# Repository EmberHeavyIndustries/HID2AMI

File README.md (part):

## ** Preassembled units **: If you are interested in ready-to-go pre-assembled units, a small number of them is available from time to time, assembled by various users/hobbyists. You can look for one on Amibay's thread [link] and check if there is any available on sale (https://www.amibay.com/threads/new-hid2ami-v3-1-0-mousewheel-support-personality-switch-hid-mouse-and-gamepad-to-amiga-adaptor.2451017/) 

||||
| ------------------------------ | ---------------------------------------------- | --------------------------- |

**HID2AMI** is an **HID mouse to quadrature waveform converter** and **HID Gamepad adapter** for the Amiga (and C64, Atari 7600, AtariST also..) series of boards; it allows ANY modern HID mouse (not limited to PS/2-USB) and almost ANY (*) modern digital/analog Gamepad to be connected and enjoyed with our Amiga computers.

(*) At the moment it has been tested against dozens of different gamepads,  but working for each and every existing Gamepad cannot be guaranteed; nevertheless, if you find a Pad which does not work with HID2AMI, you are encouraged to contact the author and supply him its "HID Report Descriptor" to be investigated.

[HOW TO SUBMIT AN HID DUMP ](https://github.com/EmberHeavyIndustries/HID2AMI/blob/master/Docs/hid.dump.howto.md)

## **ENABLING MOUSEWHEEL SUPPORT**

In order the mousewheel events to be recognized from Amiga side, a proper driver has to be installed on Amiga.

The driver is freely available, and can be downloaded from the FIRMWARE folder on this github

## **REV 3.1 board** 

HID2AMI Rev. 3.1 board (released in February 2025) upgrades previous versions by compacting the size and layout to the tiniest possible, plus adding the capability to switch firmware functions on the fly.

Rev. 3.1.0 comes with the new fromware v4.0.0 which adds the capability to switch among AMIGA - ATARI_ST - C64 behavior, with peculiar features for each.
All V4.x series firmwares will be backward compatible with V2 and V1 boards

|      Personality      |         SW1 | SW2  | SW3          |           Notes                                    | 
| --------------------- |      :---:  | :---:| :---:        |        ---                                         |  
| Amiga                 |         OFF |  OFF |   X          | Default Classic HID2AMI                            | 
| Atari ST              |         ON  |  OFF |   X          | ST Mouse and Joystick/Joypad                       |
| C64                   |         OFF |  ON  |   X          | C64 Joystick/Joypad with 2nd button                |
| CONTROLLER PRIORITY   |          X  |   X  |   OFF/ON     | J->M->K / K->J->M 	                             |

## **Lemaru's shell case (Rev 3.x boards only)** 

Thanks to the talented friend Lemaru, an awesome cover is available for everyone.

You are free to download the stl/step files linked below, and print your own copy of this awesome accessory !

[ShellBox30 Top](https://github.com/EmberHeavyIndustries/HID2AMI/blob/master/Docs/HID2AmiV3_Base.stl)

[Shellbox30 Bottom](https://github.com/EmberHeavyIndustries/HID2AMI/blob/master/Docs/HID2AmiV3_Lid.stl)

## **REV 2.0 board** 

HID2AMI Rev. 2.0 board (released in Autumn 2022) upgrades previous versions by adding capability of supporting Mousewheel and CD32 protocols, in a smaller compact shape.

Current firmware v3.0.0 act in the very same way of v1.x.x, with Mousewheel support (CD32 support  will be added in future releases)

!
!
!

(Transparent shellcase images courtesy by IAmAddict)

## **NEW v3.0.0 FIRMWARE WITH MOUSEWHEEL SUPPORT** 

Starting from v3.0.0 firmware, support for mousewheel to ANY adapter hw revision (v1.0, v1.1, V2.0) has been added.

The firmware can be directly flashed on all revisions, and enables native Mousewheel support in v2.0.

In order to enable Mousewheel support on v1.x revisions, a couple of little hacks must be performed on the boards.
The hacks to be performed are: 
- short two adiacent pins of the STM32 microprocessr, by mean of a tiny drop of solder alloy (see pic)
- remove Q2 mosfet and shorten two of the pads (see pic)

After the mod, mousewheel works in v1.x all the same way it works in v2.0.
Though the mod is quite trivial, it need a minimal soldering experience.
I cannot be held responsible if anybody damages his board(s) while not properly performing the mod.

In order the mousewheel events to be recognized from Amiga side, a proper driver has to be installed on Amiga.

The driver is freely available, and can be downloaded from the FIRMWARE folder on this github

## **REV 1.1 board** 

## **Ember Heavy Industries's official Open source shell case (Rev 2.x boards only)** 

You are free to download the stl/step files linked below, and print your own copy of this beautiful shell cover !

(Sample 3D print by Solaris104)

(Sample 3D print by IAmAddicted)

[ShellBox Top](https://github.com/EmberHeavyIndustries/HID2AMI/blob/master/Docs/HID2AMI_ShellUpper.stl)

[Shellbox Bottom](https://github.com/EmberHeavyIndustries/HID2AMI/blob/master/Docs/HID2AMI_ShellLower.stl)

## **CERV's free shell case (Rev 2.x boards only)** 

User Cerv kindly designed and shared his alternative box design !

[ShellBox Cover](https://github.com/EmberHeavyIndustries/HID2AMI/blob/master/Docs/HID2AMI_CERV_cover.stl)

[Shellbox Case](https://github.com/EmberHeavyIndustries/HID2AMI/blob/master/Docs/HID2AMI_CERV_box.stl)

## **Ember Heavy Industries's official Open source shell case (Rev 1.1 boards only)** 

#### Based upon Lemaru's shell, with some enhancements and eye-catching HID2AMI logo carved on top  !

You are free to download the stl/step files linked below, and print your own copy of this beautiful shell cover !

[ShellBox Top](https://github.com/EmberHeavyIndustries/HID2AMI/blob/master/Docs/88.EmberHID2AMI.UpperShell_1.stl)

[Shellbox Bottom](https://github.com/EmberHeavyIndustries/HID2AMI/blob/master/Docs/88.EmberHID2AMI.LowerShell_1.stl)

## **GothDevil's Open source shell case (Rev 1.1 boards only)** 

#### Thanks to the talented and friendly user **GothDevil** for creating and sharing her precious work  !

You are free to download the stl/step files linked below, and print your own copy of this beautiful shell cover !

[ShellBox Top](https://github.com/EmberHeavyIndustries/HID2AMI/blob/master/Docs/top_cover_final.stl)

[Shellbox Bottom](https://github.com/EmberHeavyIndustries/HID2AMI/blob/master/Docs/bottom_cover_final.stl)

#### GothDevil kindly allows free and open distribution of this excellent work; nevertheless I (EmberHeavyIndustries) would consider it fair if anyone who enjoys her effort would give her a little donation (say: 1 EUR) to thank her for sharing.
Please send donations to GothDevil's paypal account here:

| ||Thank you GothDevil !|
| ------------------------------ | ---------------------------------------------- | --------------------------- |

## **Lemaru's Open source shell case (Rev 1.1 boards only)** 

#### Thanks to the talented and friendly user **Lemaru** for creating and sharing his precious work  !
!

You are free to download the stl/step files linked below, and print your own copy of this beautiful shell cover !

[ShellBox Top](https://github.com/EmberHeavyIndustries/HID2AMI/blob/master/Docs/HID2AMI_Top.stl)

[Shellbox Bottom](https://github.com/EmberHeavyIndustries/HID2AMI/blob/master/Docs/HID2AMI_Bottom.stl)

## **HOW DOES IT WORK** (in brief):

HID2AMI recognizes and manages any HID device connected to its USB interface; if the device is recognized as an HID mouse, then HID2AMI starts capturing live movements and button pressings of the peripheral, then converting both of them into proper quadrature waveforms (and Amiga mouse button pressings) which can be properly understood by the Amiga itself, as if a real quadrature "Amiga" mouse was connected.

If the device is recognized as an HID gamepad, then HID2AMI maps pad's controls on the Amiga Joystick port/interface.
Gamepad's buttons are mapped evenly on Amiga button1/button2/UP/DOWN (useful for jump & racing games) inputs.
Starting from fw 1.7.1 a custom mapping can be freely configured and stored for automatic retrieval upon reconnection.

There is no need to manually configure the emulation mode: device recognition and operation mode switching are automatically performed by HID2AMI itself.

## **GETTING STARTED AND USER GUIDE**:

Here you can find a quick user guide, describing basic operations and the available meta-commands for peripheral's profile customization, storage and retrieval.

[HID2AMI QUICK USER GUIDE](https://github.com/EmberHeavyIndustries/HID2AMI/blob/master/Docs/Quick.User.Guide.md)

## **COMPATIBILITY LIST**

(!) HID2AMI has been tested against a number of HID compliant Mice and Gamepads; the following compatibility list keeps track of tested peripherals. If you tested your mice/Gamepads and want to contribute to the list, simply send an email to the author with your compatibility results. In case your device is not handled properly, you can submit an HID dump to the author for investigation.  
[HOW TO SUBMIT AN HID DUMP ](https://github.com/EmberHeavyIndustries/HID2AMI/blob/master/Docs/hid.dump.howto.md)

Thanks !

|      Device      |                Model               | Min required fw ver. | Working |                Notes                 |     |
| ---------------- | ---------------------------------  |----------- | ------- | -------------------------------------| --- |
| Mice             | Any HID Compliant Mouse            |  v1.0.0    |  YES    | Any HID mouse                        ||
| Mouse            | New USB Tank Mouse                 |  v1.0.0    |  YES    |                                      ||
| Mouse            | Anker Ergonomic Vertical Mouse     |  v1.8.4    |  YES    |                                      ||
| Mouse            | Labtec Optical Mouse 600           |  v1.8.4    |  YES    |                                      ||
| Mouse            | Logitech B100                      |  v1.0.0    |  YES    |                                      ||
| Mouse            | Logitech M570                      |  v1.0.0    |  YES    |                                      ||
| Mouse            | Logitech G5   Gaming Mouse         |  v1.8.6    |  YES    |                                      ||
| Mouse            | Logitech G502 Gaming Mouse         |  v1.8.6    |  YES    |                                      ||
| Mouse            | Logitech G Pro Gaming Mouse        |  v1.8.6    |  YES    |                                      ||
| Mouse            | Logitech LIFT Vertical Mouse       |  v1.8.6    |  YES    |                                      ||
| Mouse            | Logitech MX510 MX518 G305 G203 G300 G40X G603 G70X G903 RX250     |  v1.8.7    |  YES    |     ||
| Mouse            | Logitech M-BT83 Wired Mouse        |  v1.9.2    |  YES    |                                      ||
| Mouse            | Logitech Performance MX BT         |  v1.8.7    |  YES    |                                      ||
| Mouse            | Logitech Wireless Mouse M220, M305, M560, M70X    |  v1.7.4    |  YES    |                             ||
| Mouse            | Logitech Wireless Mouse M590       |  v1.8.4    |  YES    |                                      ||
| Mouse            | Logitech Wireless Mouse Mx Master  |  v1.8.4    |  YES    |                                      ||
| Mouse            | Microsoft Classic Intellimouse 2018|  v1.8.c    |  YES    |                                      || 
| Mouse            | Microsoft Intellimouse             |  v1.6.0    |  YES    | Not 100% HID protocol compliant      || 
| Mouse            | Microsoft Intellimouse Explorer    |  v1.8.4    |  YES    | Wireless explorer series             ||
| Mouse            | Microsoft Wireless Laser 6000, 7000|  v1.8.4    |  YES    | Wireless explorer series             ||
| Mouse            | Rapoo 7100P  Wireless Mouse        |  v1.8.6    |  YES    |                                      ||
| Mouse            | Steelseries Rival 100 and 110      |  v1.8.6    |  YES    |                                      ||
| Mouse            | Steelseries Rival 310              |  v1.8.6    |  YES    |                                      ||
| Mouse            | Steelseries Rival 500              |  v1.8.6    |  YES    |                                      ||
| Mouse            | Steelseries Rival 600              |  v1.8.7    |  YES    |                                      ||
| Mouse            | Targus Mini Mouse                  |  v1.7.4    |  YES    | Not 100% HID protocol compliant      ||
| Mouse            | Trust Wireless 18519 YVI           |  v1.8.8    |  YES    |                                      ||
| Mouse            | Yenkee YMS 3007                    |  v1.8.4    |  YES    |                                      ||
| Gamepad          | 8bitd0 SFC30 Bluetooth             |  v1.8.0    |  YES    |                                      ||
| Gamepad          | 8bitd0 M30 Wireless 2.4G           |  v1.8.0    |  YES    |                                      ||
| Adapter          | 8bitd0 Wireless adapter 2.4G       |  v1.8.0    |  YES    | All wireless controllers (xbox ONE, etc) ||
| Joystick         | Arcade Stick w/ USB encoder        |  v1.3.0    |  YES    | Stick is digital only                ||
| Joystick         | C64 Mini Stick                     |  v1.3.0    |  YES    | Stick is digital only                ||
| Gamepad          | Diswoe Wireless PC/Nintendo Switch |  v1.8.0    |  YES    |                                      ||
| Gamepad          | Dual Stick China Clone             |  v1.3.0    |  YES    | Both digital and analog mode         ||
| Gamepad          | Dual Wireless PS3-USB or BT        |  v1.9.8    |  YES    | Both digital and analog mode  (3)    ||
| Gamepad          | Hama Whitestorm                    |  v1.3.0    |  YES    | Both digital and analog mode         ||
| Joystick         | HORI FightingStick Mini            |  v1.8.0    |  YES    | Both PS3 and PS4 mode                ||
| Gamepad          | Logitech PS2 Wireless              |  v1.3.0    |  YES    | Both digital and analog mode         ||
| Gamepad          | Logitech Rumble Gamepad F310       |  v1.6.0    |  YES    | Both PC and XBOX 360 mode            ||
| Gamepad          | Logitech Rumble Gamepad F510       |  v1.6.0    |  YES    | Both PC and XBOX 360 mode            ||
| Gamepad          | Logitech Rumblepad 2               |  v1.3.0    |  YES    | Both digital and analog mode         ||
| Gamepad          | Logitech Wingman Rumblepad         |  v1.3.0    |  YES    | Both digital and analog mode         ||
| Gamepad          | Logitech Wireless Gamepad F710     |  v1.8.0    |  YES    | Both PC and XBOX 360 mode            ||
| Gamepad          | PS3/PC Clones                      |  v1.5.2    |  YES    | Both digital and analog mode         ||
| Gamepad          | RetroLink Classic Controller USB   |  v1.8.0    |  YES    | (Sega Saturn Style)                  ||
| Gamepad          | SEGA Mega Drive Mini USB Pad       |  v1.9.1    |  YES    |                                      ||
| Joystick         | SEGA VirtuaStick High Grade        |  v1.8.0    |  YES    | PS3 mode - Stick is digital only     ||
| Gamepad          | Sony PS1 original pad              |  v1.6.0    |  YES    | With USB adapter                     ||
| Gamepad          | Sony PS2 original pad              |  v1.6.0    |  YES    | With USB adapter                     ||
| Gamepad          | Sony PS2 original pad              |  v1.8.1    |  YES    | With DUAL USB adapter (1)            ||
| Gamepad          | Sony PS-ONE original pad           |  v1.6.0    |  YES    | With USB adapter                     ||
| Gamepad          | Sony Dual Shock 3 PS3 original pad |  v1.8.b    |  YES    | With USB cable or BT **WARNING !! (2) (3)**  ||
| Gamepad          | Sony Dual Shock 4 PS4 original pad |  v1.8.0    |  YES    | **WARNING !! (2)**                   ||
| Gamepad          | SNES Usb Clone                     |  v1.3.0    |  YES    | Pad is digital only                  ||
| Joystick         | Speedlink Competition PRO USB      |  v1.8.0    |  YES    |                                      ||
| Gamepad          | Speedlink TORID WL			        |  v1.8.0    |  YES    | Put in XInput mode                   ||
| Gamepad          | Thrustmaster Firestorm Digital     |  v1.3.0    |  YES    | Pad is digital only                  ||
| Joystick         | Thrustmaster T-16000M              |  v1.8.0    |  YES    |                                      ||
| Gamepad          | Thrustmaster Wireless dual trigger |  v1.3.0    |  YES    | Both digital and analog mode         ||
| Gamepad          | XBOX 360 Clone                     |  v1.6.0    |  YES    | Not HID protocol compliant           | 
| Gamepad          | XBOX Elite                         |  v1.8.0    |  YES (*) |(*) works via 8bitdo Wireless dongle |
 
 (1) Plug the pad in adaptor #1 port
 
 (2) **WARNING! If using the wired version, either remove internal battery (suggested) or be sure it is 100% charged before connecting to your Amiga**
 
 (3) Click d-pad (Hat) soon after connection to start auto-reconfiguration of the pad

 ## **HW AND SCHEMATICS**
  
|   Flavour      | Current ver.  |                Features               |
| -------------- | ------------- | ------------------------------------- |
| HID2AMI LITE   |    v1.0.0     |   direct output to Amiga port lines   |
| HID2AMI DeLuxe |    v1.1.0     |   output lines driven by mosfet       |
| HID2AMI DeLuxe |    v2.0.0     |   compact size, reduced mosfets       |

## **FIRMWARE**
  
|      Baseline        		| Current ver.  |                Features              |
| -------------------- 		| ------------- | -------------------------------------|
| HID2AMI BOOTLOADER   		|    v1.4.0     |   Enables DFU upgrade of APP         |
| HID2AMI OEM BOOTLOADER   	|    v1.4.0     |   Enables DFU upgrade of APP         |
| HID2AMI APP          		|    v4.0.3   	|   see release notes below            |

Features of fw v4.04
 - Fixed further line driving in ODmode for "weak" C64 consoles [no more "locked last keyb row"]
 - Added gaming numpad support [SWOS edition] 
 - Extended keyboard decoding up to three keys at the same time [SWOS edition]
 - Denied conflicting direction with keyb (L+R and U+D) [SWOS eidiotn - fix for Amiga orignal SWOS game's bug]
 - Added forcing Razer DeathStalker V2 to Keyboard [SWOS edition]
 - Added support for Shenzhen Evision Semiconductor Technology Wireless adapter for Mouse (Aliexpress)
 - Added priority input selector for multi-device-cntrollers (default priority is Joy->Mouse->Keyboard, alternate is Keyboard->Joy->Mouse)

|      Personality      |         SW1 | SW2  | SW3          |           Notes                                    | 
| --------------------- |      :---:  | :---:| :---:        |        ---                                         |  
| Amiga                 |         OFF |  OFF |   X          | Default Classic HID2AMI                            | 
| Atari ST              |         ON  |  OFF |   X          | ST Mouse and Joystick/Joypad                       |
| C64                   |         OFF |  ON  |   X          | C64 Joystick/Joypad with 2nd button                |
| CONTROLLER PRIORITY   |          X  |   X  |   OFF/ON     | J->M->K / K->J->M 	                             |

Features of fw v4.03
 - Added customizable keyboard mapping (SWOS edition)
 - Fixed C64 mode keyb conflict
 - Fixed Mouse scroll down not working in some PiStormed A1200

Features of fw v4.0.2
-	SWOS edition
-	Enabled USB keyboard support

Features of fw v4.0.1
 - 	Added Razer Steel Series Rival 3 Mouse support

Features of fw v4.0.0
 - 	HRW v3.x support - full backward compatibility with v2.x and v1.x (v1.x need scrollwheel hw hack)
 - 	HRW v3.x personality mode switch AMIGA-ATARI-C64
   
|      Personality      |  Switch position 0     1     2             | Notes                                              |
| --------------------- | --------------------------------- |--------------------------------------------------- |
| Amiga                 |         OFF   OFF   OFF           | Default Classic HID2AMI                            | 
| Atari ST              |         ON    OFF   OFF           | ST Mouse and Joystick/Joypad                       |
| C64                   |         OFF   ON    OFF           | C64 Joystick/Joypad with 2nd button                |

Features of fw v3.0.5
 - 	Added flash storage for PS4 controllers mapping
 - 	Added Logitech VX Nano support
 - 	Added Logitech G403 Hero support
 - 	Added Advanced Corded Mouse M500s support
 - 	All Logitech wireless dongles default to mouse

Features of fw v3.0.4
 - Fixed an elusive bug that activated the multiplier setup mode each time the power was turned back on
 - Fixed a bug where changing mouse pointer direction after a stop. Mouse movements are now pixel perfect

Features of fw v3.0.3
 - Maintenance release
   
Features of fw v3.0.2
 - Added support for Logitech G602, G9x, G700
 - Added support for Razer DeathAdder 2013
 - Added support for Dell Wireless Mouse (from set KM3322W)
 - Added support for X8 mouse speed demultiplier (1000dpi + mice)
 - Added support for "Mad Catz" Speedlink competition pro

Features of fw v3.0.1
 - Enabled management of 3rd mouse button in conjunction with MouseWheel
 
Features of fw v3.0.0
 - Unified firmware for all HID2Ami revisions, compatible with v1.0, v1.1, v2.0
 - Add mousewheel support on all Amigas (V2.0)
 - Add mousewheel support with v1.x boards + hw fix
 
Features of fw v1.9.8
 - Added support for Microsoft Wireless Mobile Mouse 4000
 - Added support for Logitech MX Revolution Mouse
 - Added support for Logitecg G400 Gaming Mouse
 - Added support for Logitech G700 Laser Mouse
 - Added support for Logitexh MX Master 3S
 - Added support for PS3 DualShock3 BT adapter plus coded trick to detect USB o BT connection (move hat soon after connecting)
 - Fixed deadzone values for XBOX360 pads

Features of fw v1.9.7:
 - Added full mapping support for XBox360 and compatible pads
 
Features of fw v1.9.6:
 - Added support for cursor arrow keys in keyboard driver
 - Joypad buttons now can be mapped either B1-B2-UP-DN or B1-B2-B1-B2 (the latter by pressing LEFT direction while mapping) 
 - Added MS Touch Wireless Mouse support
 - Added MS BTechnology wireless adapter
 - Fixed a custom HID mouse protocol init bug (greatly improves compatiiblity with non standard HID devices) 

Features of fw v1.9.5:
 - Added support for Logitech B170 / M170 wireless adapters and peripherals
 - Added generic support for composite (multi-peripheral) Logitech devices
	
Features of fw v1.9.4:
 - Fixed a very stupid bug, which caused quadrature waveform emulation non behaving correctly.
        Though anybody noticed it (not even myself until now !), the fixed quadrature waveform now performs
        way smoother pointer movements. 
	
Features of fw v1.9.3:
  - Added support for SpeedLink Competition Pro USB 2019+
  - Fixed a stupid bug not clearing device mapping upon disconnection (very hardly to occur, indeed)
 
Features of fw v1.9.2:
  - Added support for Logitech M-BT83 Wired Mouse 
   
Features of fw v1.9.1:
  - Added support for SEGA Mega Drive Mini USB Adapters 

Features of fw v1.9.0:
  - Added support for HID keyboards with "WADS" mapping 

Features of fw v1.8.c:
  - Added support for Microsoft Classic Intellimouse 2018 

Features of fw v1.8.b:
  - Added support for Sony PS3 Dualshock3 PAD

Features of fw v1.8.a:
  - Fixed a stupid bug which prevented 16-bit-axis mice to be correctly managed

Features of fw v1.8.9:
 - Changed mousewheel behaviour: 
   - 1. Defaults to no action [hint: probably adding freemouse support in one of next updates]
   - 2. Pressing all three mouse buttons together, board enters "pointer speed setting" mode [Led stops blinking->firmly lit]
   - 3. Rolling Mousewheel now changes pointer speed / DPI sensitivity
   - 4. Pressing all three button together again will save current setting and return to default behaviour [Led starts blinking again]
 - Added support for Logitech MK250
 - Added support for RAPOO 5G Wireless Mouse
 - Added support for ATARI ST Mouse port (ALL devices)
 
Features of fw v1.8.8:
- Added support for Trust IVY 18519 Wireless Mouse
- Added support for Logitech M305 BT Wireless Mouse

Features of fw v1.8.7:
- Added support for Logitech MX510 MX518 G305 G203 G403 G603 G703 G903 gaming mice
- Added support for SteelSeriec Rival 110 and 600 Gaming mice
 
Features of fw v1.8.6:
- Added support for Logitech G502, G5 and G Pro Gaming mice
- Added support for SteelSeriec Rival 100, 310 and 500 Gaming mice

Features of fw v1.8.5:
- Added automatic recognition and management of hw customized report Id (improves compatibility)

Features of fw v1.8.0:
- Added support for PS3 and PS4 3rd party compatible pads 
- Added support for original Dual Shock 4 PS4 pads
- Reworked 12-bit XY axis support for gaming/precision mice
- Improved compatibility with some Logitech gaming mice

Features of fw v1.7.4:
- Added support for Logitech M560 Wireless Mouse
- 	Added support for Targus MiniMouse
- 	Added multiple HID device interface support (greatly improves compatibility)
-	Added preliminary Microsoft Wireless Laser Mouse 6000 support
- Added preliminary support to XBOX ONE gamepads

Features of fw v1.7.3:
- Added custom free mapping of first 4 buttons of Gamepad. By pressing 4buttons+LeftStickDown the board enters in mapping mode; pressing in turn single buttons maps them on Amiga1->Amiga2->Up->Down
- Added custom mapping config autosave: each custom configuration is permanently stored and recalled upon Gamepad reconnection.
- Separate permanent configs (up to 20) are saved and recalled automatically upon recognition of Gamepads brand/model
- Added support for 12 bit high resolution gaming mice
- Added customizable real-time mouse pointer speed adjust, by rolling the mousewheel forward/backwards
- Added save of permanent config for mouse pointer speed, by pressing L-M-R buttons together 

Features of fw v1.7.1:
- Added mapping of DWN/backward to Gamepad 4th button. Buttons are now evenly mapped according P1->P2->UP->DWN sequence;
- User can swap UP<->DWN button mapping by simultaneously pressing first 4 pad's buttons;

Features of fw v1.6.2:
- Added mapping of UP/Forward to Gamepad 3rd button;
- Optimized gamepad decoding core, even faster response;

Features of fw v1.6.0:
- Added support for XBOX 360 Gamepad clones;
- Added support for MS Intellimouse;

Features of fw v1.5.2: 
- Unified firmware, self configuring according to board variant (Lite or DeLuxe);
- Automatic recognition of any HID mouse;
- Automatic recognition of any (!) HID joystick/gamepad;
- Full support for both USB 1.1 and USB 2.0 periperhals;
- Support for both digital (hatswitch) and analog x-y gamepad axis;
- Automatic emulation mode switch upon peripheral connection (no need of any manual settings);
- Self discover and mapping of pad buttons (limited to first 6);
- Easy firmware upgrade through (windows) PC USB interface;

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
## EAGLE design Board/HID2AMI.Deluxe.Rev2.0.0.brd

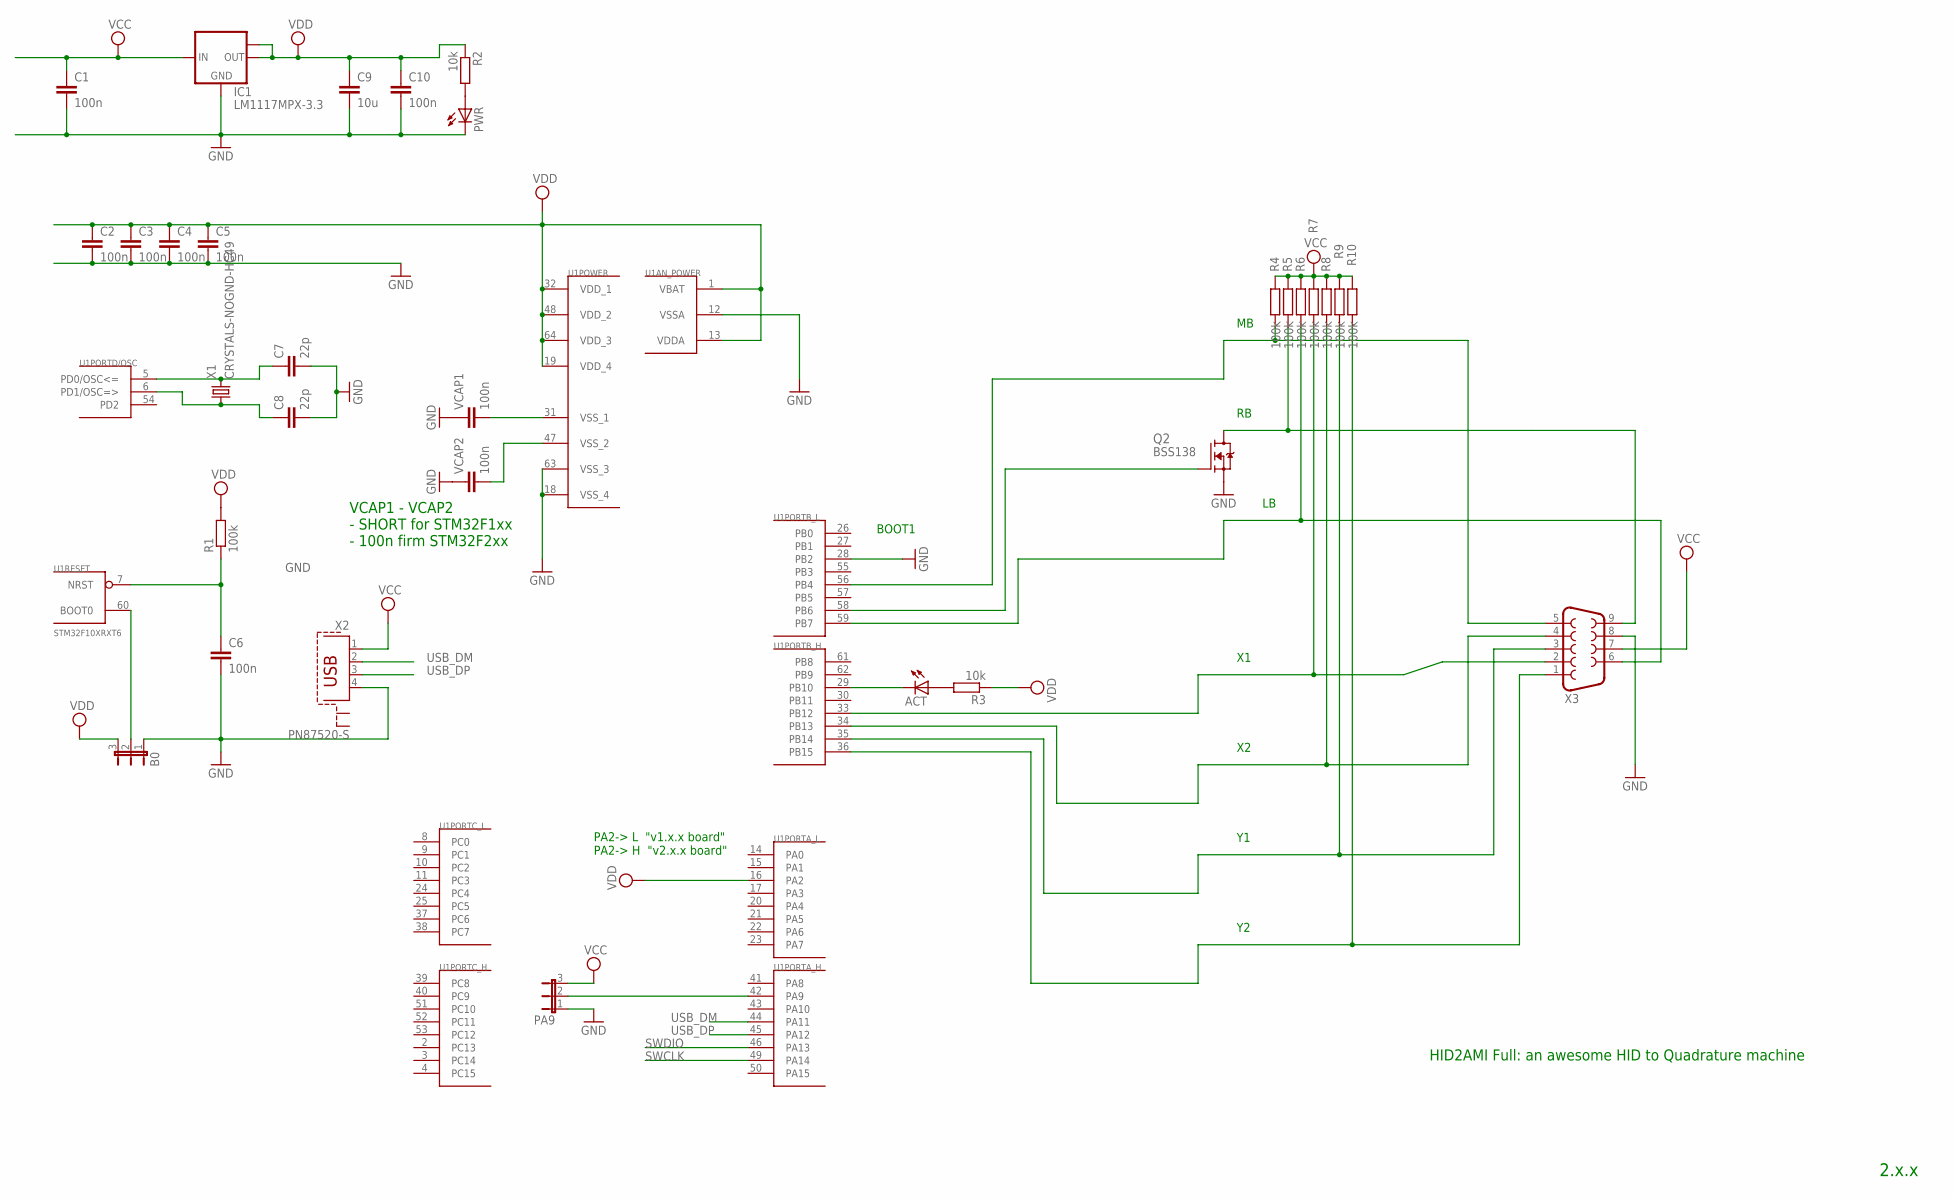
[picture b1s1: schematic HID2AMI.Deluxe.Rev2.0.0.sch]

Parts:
ACT: LEDSML0805; SML0805
B0: JP2E; JP2
C1, C2, C3, C4, C5, C6, C10: 100n; C0805
C7, C8: 22p; C0805
C9: 10u; C0805
IC1: LM1117MPX-3.3; SOT223
PA9: JP2E; JP2
PWR: LEDSML0805; SML0805
Q2: BSS138; SOT23
R1, R4, R5, R6, R7, R8, R9, R10: 100k; M0805
R2, R3: 10k; M0805
U1: STM32F10XRXT6; TQFP64
VCAP1, VCAP2: 100n; C0805
X1: CRYSTALS-NOGND-HC49; HC49
X2: PN87520-S
X3: F09HP

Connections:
ACT: R7.2, U1.33 (PB12), X3.2
GND: B0.1, C1.2, C2.2, C3.2, C4.2, C5.2, C6.2, C7.2, C8.2, C9.2, C10.2, IC1.1 (GND), PA9.1, PWR.C, Q2.2 (S), U1.12 (VSSA), U1.18 (VSS_4), U1.28 (PB2), U1.63 (VSS_3), VCAP1.1, VCAP2.1, X2.4, X3.8
unnamed: C7.1, U1.5 (PD0/OSC<=), X1.2
unnamed: C8.1, U1.6 (PD1/OSC=>), X1.1
unnamed: B0.2, U1.60 (BOOT0)
unnamed: U1.31 (VSS_1), VCAP1.2
unnamed: PA9.2, U1.42 (PA9)
unnamed: U1.47 (VSS_2), VCAP2.2
unnamed: ACT.A, R3.2
unnamed: ACT.C, U1.29 (PB10)
unnamed: PWR.A, R2.2
unnamed: R4.2, U1.56 (PB4), X3.5
unnamed: Q2.1 (G), U1.58 (PB6)
unnamed: R6.2, U1.59 (PB7), X3.6
unnamed: Q2.3 (D), R5.2, X3.9
unnamed: R8.2, U1.34 (PB13), X3.4
unnamed: R9.2, U1.35 (PB14), X3.3
unnamed: R10.2, U1.36 (PB15), X3.1
NRST: C6.1, R1.1, U1.7 (NRST)
SWCLK: U1.49 (PA14)
SWDIO: U1.46 (PA13)
USB_DM: U1.44 (PA11), X2.2
USB_DP: U1.45 (PA12), X2.3
VCC: C1.1, IC1.3 (IN), PA9.3, R4.1, R5.1, R6.1, R7.1, R8.1, R9.1, R10.1, X2.1, X3.7
VDD: B0.3, C2.1, C3.1, C4.1, C5.1, C9.1, C10.1, IC1.2 (OUT), IC1.TAB (OUT1), R1.2, R2.1, R3.1, U1.1 (VBAT), U1.13 (VDDA), U1.16 (PA2), U1.19 (VDD_4), U1.32 (VDD_1), U1.48 (VDD_2), U1.64 (VDD_3)

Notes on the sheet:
2.x.x
HID2AMI Full: an awesome HID to Quadrature machine
PA2-> L "v1.x.x board" PA2-> H "v2.x.x board"
BOOT1
VCAP1 - VCAP2 - SHORT for STM32F1xx - 100n firm STM32F2xx

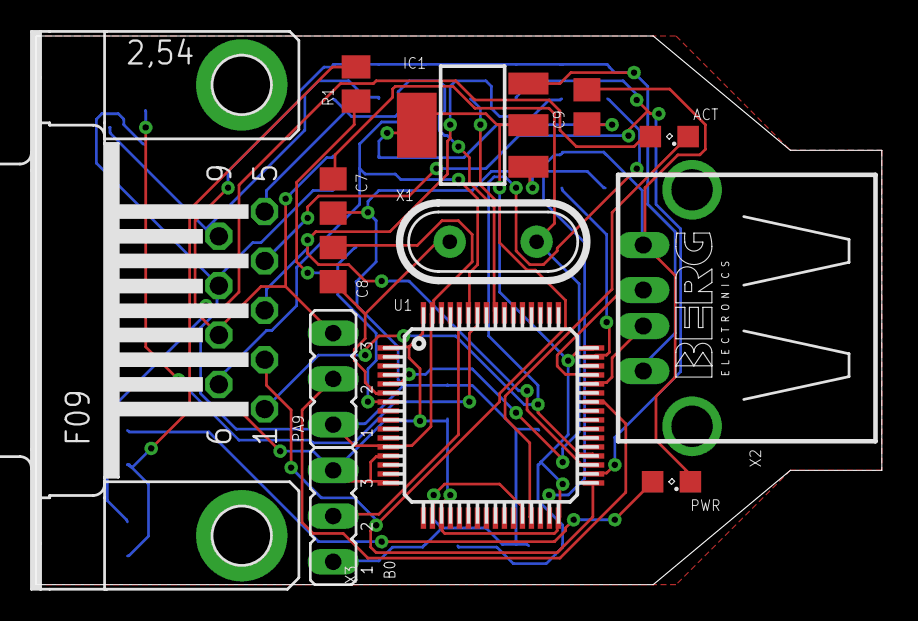
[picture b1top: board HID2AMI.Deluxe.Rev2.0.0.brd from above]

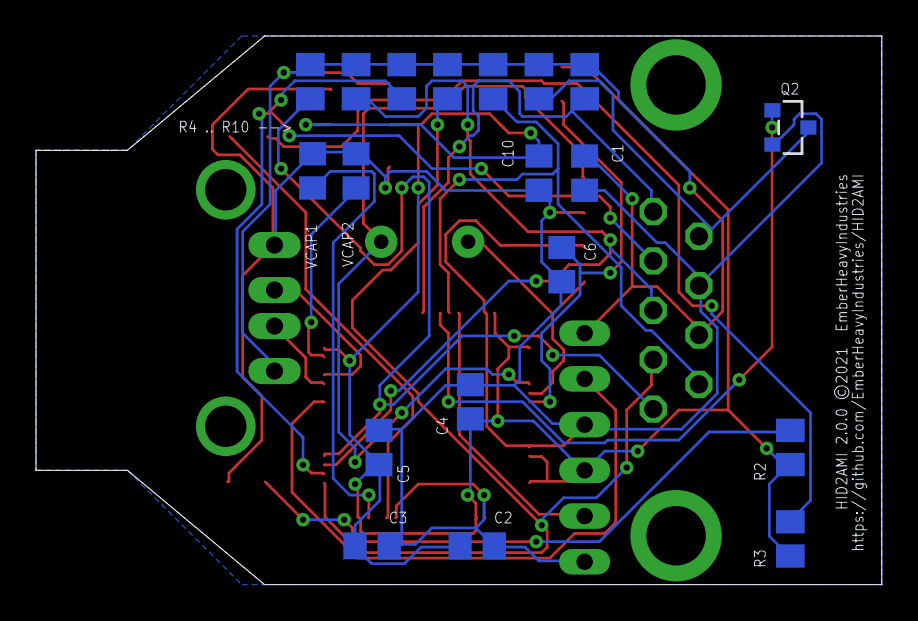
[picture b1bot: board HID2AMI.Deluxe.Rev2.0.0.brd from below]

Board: 2 copper layers, 47.0 x 30.5 mm, 32 parts (19 on the bottom side), 23 nets.

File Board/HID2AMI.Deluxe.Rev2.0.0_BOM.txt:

Partlist exported from E:/Amiga/Schematics/HID2AMI/HID2AMI.Deluxe.Rev2.0.0.sch at 11/11/2022 2:38 PM

Qty Value               Device              Package   Parts                                     Description                                                           MF        MPN    OC_FARNELL OC_NEWARK POPULARITY SPICEPREFIX
1                       F09HP               F09HP     X3                                        SUB-D                                                                                  unknown    unknown                         
2                       JP2E                JP2       B0, PA9                                   JUMPER                                                                                                      34                    
2                       LEDSML0805          SML0805   ACT, PWR                                  LED                                                                                                                               
8   100k                R-EU_M0805          M0805     R1, R4, R5, R6, R7, R8, R9, R10           RESISTOR, European symbol                                                                                              R          
9   100n                C-EUC0805           C0805     C1, C2, C3, C4, C5, C6, C10, VCAP1, VCAP2 CAPACITOR, European symbol                                                                                             C          
2   10k                 R-EU_M0805          M0805     R2, R3                                    RESISTOR, European symbol                                                                                              R          
1   10u                 C-EUC0805           C0805     C9                                        CAPACITOR, European symbol                                                                                             C          
2   22p                 C-EUC0805           C0805     C7, C8                                    CAPACITOR, European symbol                                                                                             C          
1   BSS138              BSS138              SOT23     Q2                                        BSS138 N-Channel Logic Level Enhancement Mode Field Effect Transistor Fairchild BSS138 9845330    67R2009                         
1   CRYSTALS-NOGND-HC49 CRYSTALS-NOGND-HC49 HC49      X1                                        CRYSTALS CAN NOT GROUNDED                                                                                   0                     
1   LM1117MPX-3.3       LM1117MPX-3.3       SOT223    IC1                                                                                                                                                                         
1   PN87520-S           PN87520-S           PN87520-S X2                                                                                                                               unknown    unknown                         
1   STM32F10XRXT6       STM32F10XRXT6       TQFP64    U1                                        STM32F101/103 64pin LQFP

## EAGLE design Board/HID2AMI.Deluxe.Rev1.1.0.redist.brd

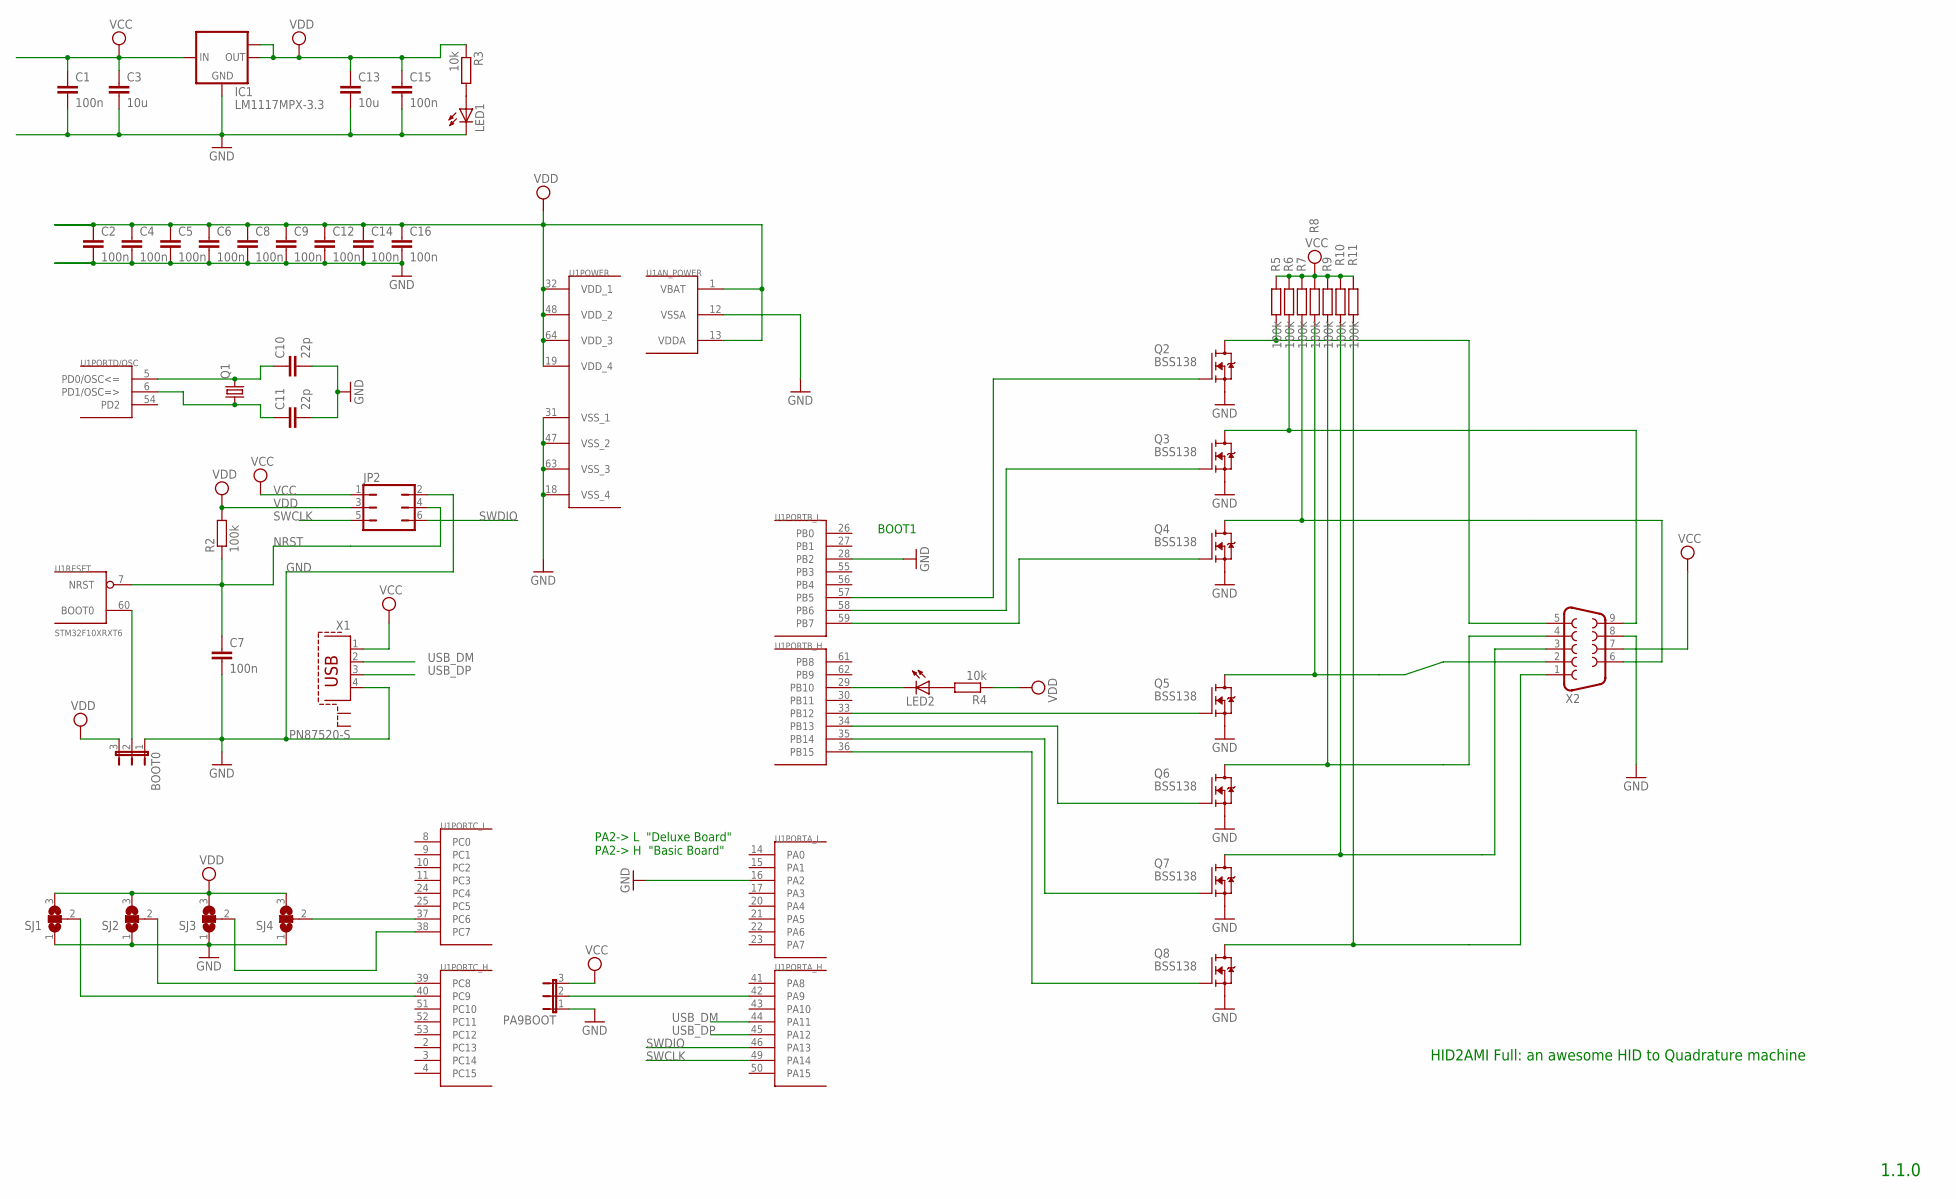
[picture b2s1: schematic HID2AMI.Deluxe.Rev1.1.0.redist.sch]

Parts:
BOOT0: JP2E; JP2
C1, C2, C4, C5, C6, C7, C8, C9, C12, C14, C15, C16: 100n; C0805
C3: 10u; C1206
C10, C11: 22p; C0805
C13: 10u; C0805
IC1: LM1117MPX-3.3; SOT223
JP2: JP3Q
LED1, LED2: LEDSML0805; SML0805
PA9BOOT: JP2E; JP2
Q1: CRYSTALHC49S; HC49/S
Q2, Q3, Q4, Q5, Q6, Q7, Q8: BSS138; SOT23
R2, R5, R6, R7, R8, R9, R10, R11: 100k; M0805
R3, R4: 10k; M0805
SJ1, SJ2, SJ3, SJ4: SJ2W; SJ_2
U1: STM32F10XRXT6; TQFP64
X1: PN87520-S
X2: F09HP

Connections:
GND: BOOT0.1, C1.2, C2.2, C3.2, C4.2, C5.2, C6.2, C7.2, C8.2, C9.2, C10.2, C11.2, C12.2, C13.2, C14.2, C15.2, C16.2, IC1.1 (GND), JP2.2, LED1.C, PA9BOOT.1, Q2.2 (S), Q3.2 (S), Q4.2 (S), Q5.2 (S), Q6.2 (S), Q7.2 (S), Q8.2 (S), SJ1.1, SJ2.1, SJ3.1, SJ4.1, U1.12 (VSSA), U1.16 (PA2), U1.18 (VSS_4), U1.28 (PB2), U1.31 (VSS_1), U1.47 (VSS_2), U1.63 (VSS_3), X1.4, X2.8
unnamed: C10.1, Q1.2, U1.5 (PD0/OSC<=)
unnamed: C11.1, Q1.1, U1.6 (PD1/OSC=>)
unnamed: BOOT0.2, U1.60 (BOOT0)
unnamed: PA9BOOT.2, U1.42 (PA9)
unnamed: SJ1.2, U1.40 (PC9)
unnamed: LED2.A, R4.2
unnamed: LED2.C, U1.29 (PB10)
unnamed: SJ4.2, U1.37 (PC6)
unnamed: SJ3.2, U1.38 (PC7)
unnamed: SJ2.2, U1.39 (PC8)
unnamed: LED1.A, R3.2
unnamed: Q2.1 (G), U1.57 (PB5)
unnamed: Q3.1 (G), U1.58 (PB6)
unnamed: Q4.1 (G), U1.59 (PB7)
unnamed: Q5.1 (G), U1.33 (PB12)
unnamed: Q6.1 (G), U1.34 (PB13)
unnamed: Q7.1 (G), U1.35 (PB14)
unnamed: Q8.1 (G), U1.36 (PB15)
unnamed: Q2.3 (D), R5.2, X2.5
unnamed: Q3.3 (D), R6.2, X2.9
unnamed: Q4.3 (D), R7.2, X2.6
unnamed: Q5.3 (D), R8.2, X2.2
unnamed: Q6.3 (D), R9.2, X2.4
unnamed: Q7.3 (D), R10.2, X2.3
unnamed: Q8.3 (D), R11.2, X2.1
NRST: C7.1, JP2.4, R2.1, U1.7 (NRST)
SWCLK: JP2.5, U1.49 (PA14)
SWDIO: JP2.6, U1.46 (PA13)
USB_DM: U1.44 (PA11), X1.2
USB_DP: U1.45 (PA12), X1.3
VCC: C1.1, C3.1, IC1.3 (IN), JP2.1, PA9BOOT.3, R5.1, R6.1, R7.1, R8.1, R9.1, R10.1, R11.1, X1.1, X2.7
VDD: BOOT0.3, C2.1, C4.1, C5.1, C6.1, C8.1, C9.1, C12.1, C13.1, C14.1, C15.1, C16.1, IC1.2 (OUT), IC1.TAB (OUT1), JP2.3, R2.2, R3.1, R4.1, SJ1.3, SJ2.3, SJ3.3, SJ4.3, U1.1 (VBAT), U1.13 (VDDA), U1.19 (VDD_4), U1.32 (VDD_1), U1.48 (VDD_2), U1.64 (VDD_3)

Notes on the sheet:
1.1.0
HID2AMI Full: an awesome HID to Quadrature machine
PA2-> L "Deluxe Board" PA2-> H "Basic Board"
BOOT1

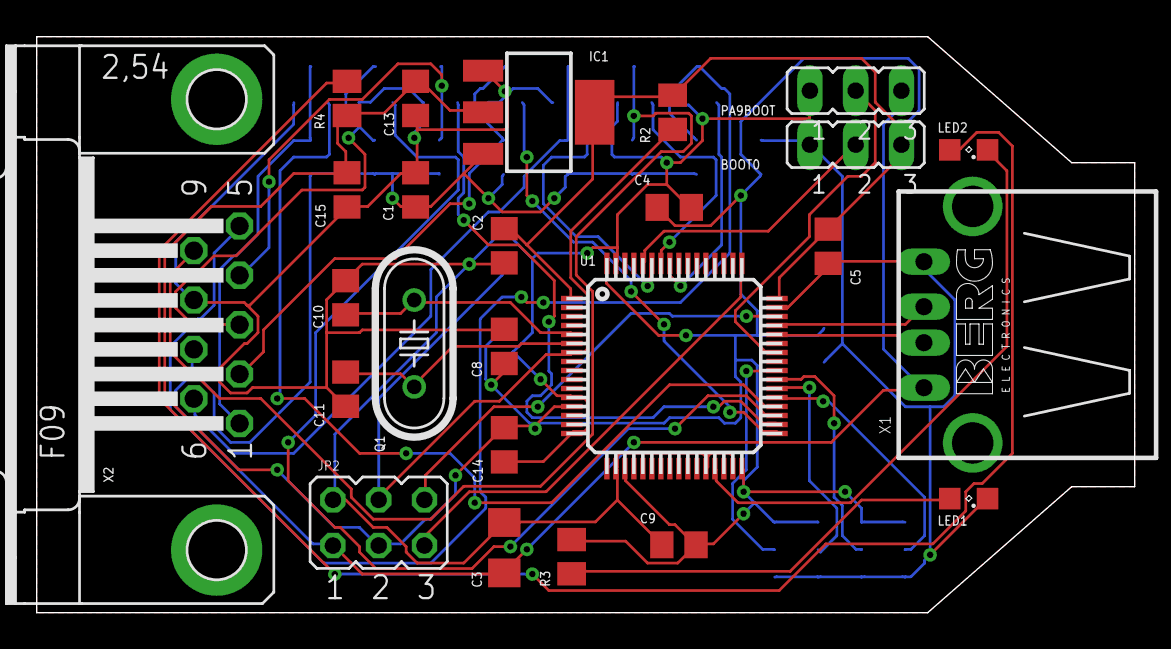
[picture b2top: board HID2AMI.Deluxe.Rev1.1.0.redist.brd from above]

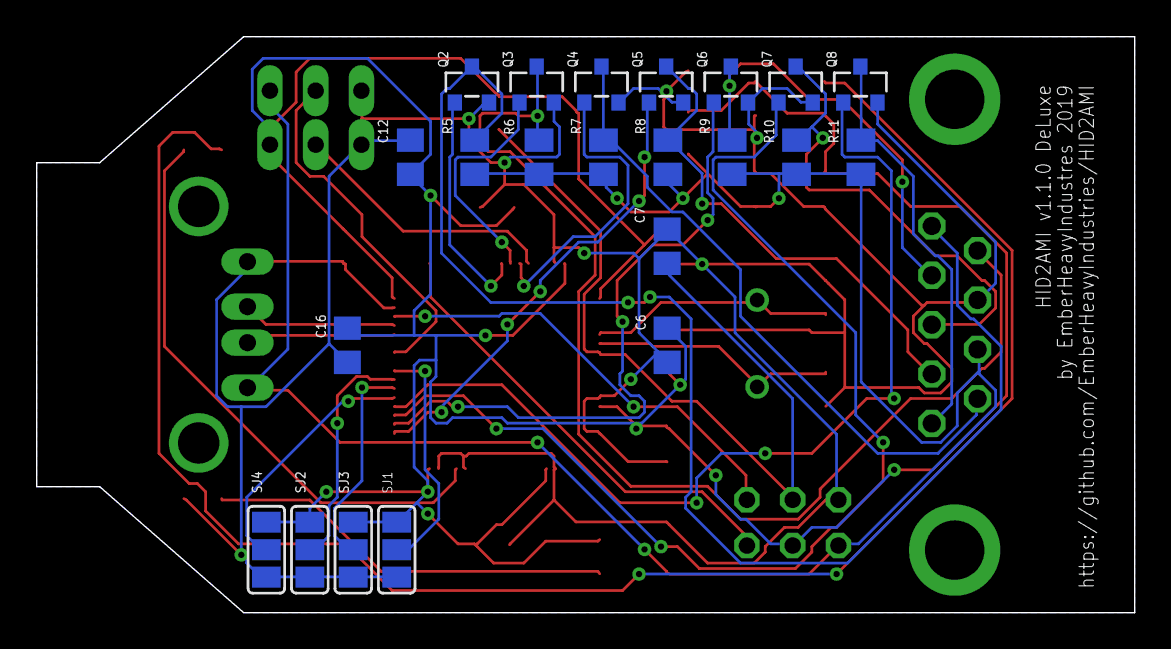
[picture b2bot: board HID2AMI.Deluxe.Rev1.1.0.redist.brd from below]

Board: 2 copper layers, 61.0 x 32.0 mm, 47 parts (22 on the bottom side), 33 nets.

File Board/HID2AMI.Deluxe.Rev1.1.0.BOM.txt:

|Part   |   Value  |     Device       |  Package   | Man./Opt.|
|-------|--------- |------------------|------------|----------|
|BOOT0  |   JP2E   |        JP1       |   JUMPER   |          |
|PA9BOOT|   JP2E   |        JP2       |   JUMPER   |          |
|       |          |                  |            |          |
|C1     | 100n     |   C-EUC0805      |  C0805     | Optional |
|C2     | 100n     |   C-EUC0805      |  C0805     | Optional |
|C3     | 10u      |   C-EUC1206      |  C1206     | Optional |
|C4     | 100n     |   C-EUC0805      |  C0805     | MANDATORY|
|C5     | 100n     |   C-EUC0805      |  C0805     | MANDATORY|
|C6     | 100n     |   C-EUC0805      |  C0805     | Optional |
|C7     | 100n     |   C-EUC0805      |  C0805     | Optional |
|C8     | 100n     |   C-EUC0805      |  C0805     | Optional |
|C9     | 100n     |   C-EUC0805      |  C0805     | MANDATORY|
|C10    |  22p     |   C-EUC0805      |  C0805     | MANDATORY|
|C11    |  22p     |   C-EUC0805      |  C0805     | MANDATORY|
|C12    | 100n     |   C-EUC0805      |  C0805     | MANDATORY|
|C13    | 10u      |   C-EUC1206      |  C1206     | Optional |
|C14    | 100n     |   C-EUC0805      |  C0805     | MANDATORY|
|C15    | 100n     |   C-EUC0805      |  C0805     | Optional |
|C16    | 100n     |   C-EUC0805      |  C0805     | Optional |
|       |          |                  |            |          |
|IC1    |LM1117-3.3|   LM1117MPX-3.3  |  SOT223    | MANDATORY|
|       |          |                  |            |          |
|LED1   |          |   LEDSML0805     |  SML0805   | Optional |
|LED2   |          |   LEDSML0805     |  SML0805   | Optional |
|       |          |                  |            |          |
|Q1     | 8MHz     |   CRYSTALHC49S   |  HC49/S    | MANDATORY|
|       |          |                  |            |          |
|Q2     | BSS138   |   BSS138         |  SOT23     | MANDATORY|
|Q3     | BSS138   |   BSS138         |  SOT23     | MANDATORY|
|Q4     | BSS138   |   BSS138         |  SOT23     | MANDATORY|
|Q5     | BSS138   |   BSS138         |  SOT23     | MANDATORY|
|Q6     | BSS138   |   BSS138         |  SOT23     | MANDATORY|
|Q7     | BSS138   |   BSS138         |  SOT23     | MANDATORY|
|Q8     | BSS138   |   BSS138         |  SOT23     | MANDATORY|
|       |          |                  |            |          |
|R1     | ---      |   --             |  --        | NA       |
|R2     | 100k     |   R-EU_M0805     |  M805      | MANDATORY|
|R3     | 10k-33k  |   R-EU_M0805     |  M805      | Optional |
|R4     | 10k-33k  |   R-EU_M0805     |  M805      | Optional |
|R5     | 100k     |   R-EU_M0805     |  M805      | MANDATORY|
|R6     | 100k     |   R-EU_M0805     |  M805      | MANDATORY|
|R7     | 100k     |   R-EU_M0805     |  M805      | MANDATORY|
|R8     | 100k     |   R-EU_M0805     |  M805      | MANDATORY|
|R9     | 100k     |   R-EU_M0805     |  M805      | MANDATORY|
|R10    | 100k     |   R-EU_M0805     |  M805      | MANDATORY|
|R11    | 100k     |   R-EU_M0805     |  M805      | MANDATORY|
|       |          |                  |            |          |
|U1     | F105RBT6 |   STM32F105RBT6  |  LQFP64    | MANDATORY|
|       |          |                  |            |          |
|X1     |          |   USB-CONNECTOR  |            | MANDATORY|
|X2     |          |   F09HP D-SUB9   |  F09HP     | MANDATORY|
|       |          |                  |            |          |

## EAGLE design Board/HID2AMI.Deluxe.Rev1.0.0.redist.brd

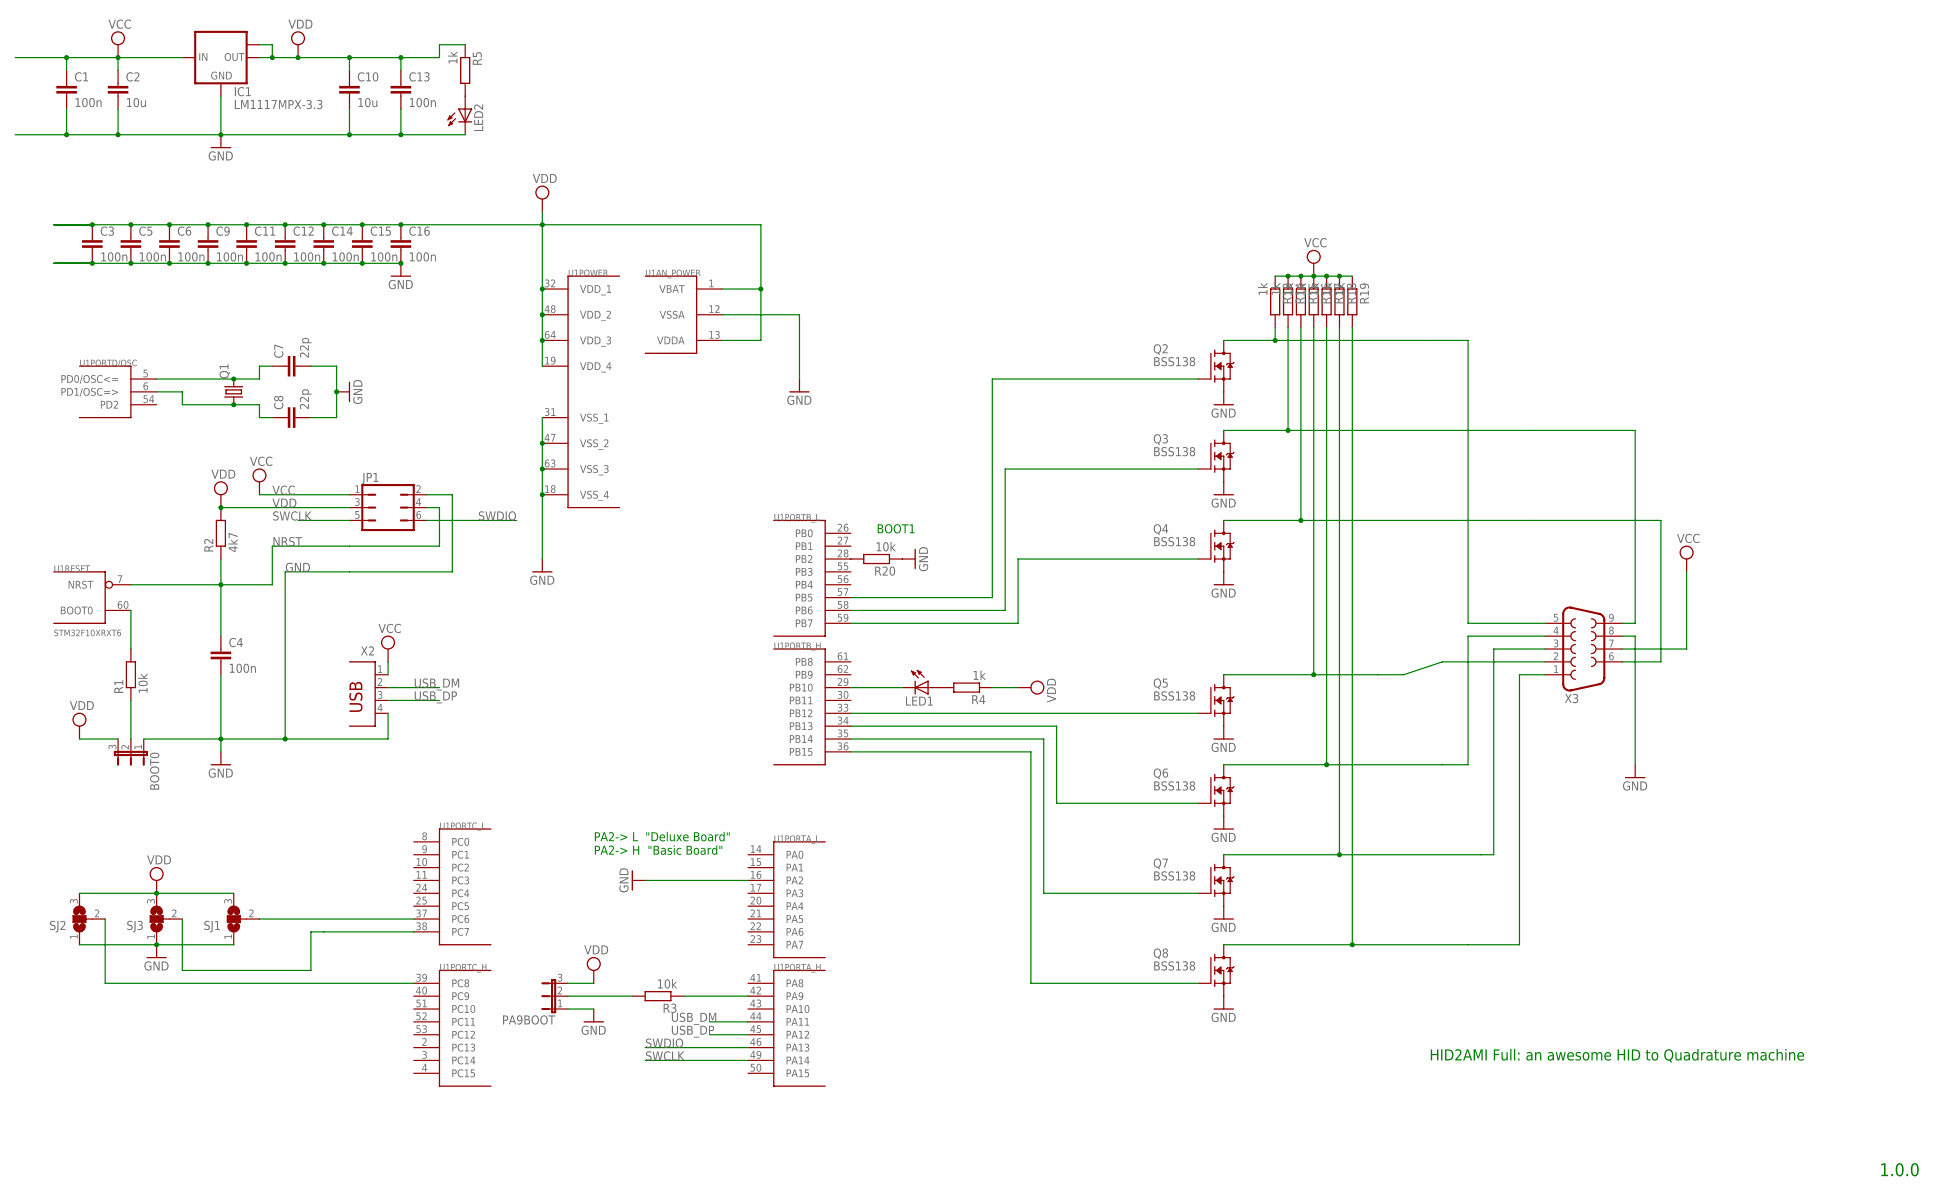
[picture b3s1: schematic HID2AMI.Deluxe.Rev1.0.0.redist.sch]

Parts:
BOOT0: JP2E; JP2
C1, C3, C4, C5, C6, C9, C11, C12, C13, C14, C15, C16: 100n; C0805
C2: 10u; C1206
C7, C8: 22p; C0805
C10: 10u; C0805
IC1: LM1117MPX-3.3; SOT223
JP1: JP3Q
LED1, LED2: LEDSML0805; SML0805
PA9BOOT: JP2E; JP2
Q1: CRYSTALHC49S; HC49/S
Q2, Q3, Q4, Q5, Q6, Q7, Q8: BSS138; SOT23
R1, R3, R20: 10k; M0805
R2: 4k7; M0805
R4, R5, R13, R14, R15, R16, R17, R18, R19: 1k; M0805
SJ1, SJ2, SJ3: SJ2W; SJ_2
U1: STM32F10XRXT6; TQFP64
X2: PN87520
X3: F09HP

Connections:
GND: BOOT0.1, C1.2, C2.2, C3.2, C4.2, C5.2, C6.2, C7.2, C8.2, C9.2, C10.2, C11.2, C12.2, C13.2, C14.2, C15.2, C16.2, IC1.1 (GND), JP1.2, LED2.C, PA9BOOT.1, Q2.2 (S), Q3.2 (S), Q4.2 (S), Q5.2 (S), Q6.2 (S), Q7.2 (S), Q8.2 (S), R20.1, SJ1.1, SJ2.1, SJ3.1, U1.12 (VSSA), U1.16 (PA2), U1.18 (VSS_4), U1.31 (VSS_1), U1.47 (VSS_2), U1.63 (VSS_3), X2.4, X3.8
unnamed: C7.1, Q1.2, U1.5 (PD0/OSC<=)
unnamed: C8.1, Q1.1, U1.6 (PD1/OSC=>)
unnamed: R1.2, U1.60 (BOOT0)
unnamed: BOOT0.2, R1.1
unnamed: PA9BOOT.2, R3.2
unnamed: R3.1, U1.42 (PA9)
unnamed: LED1.A, R4.2
unnamed: LED1.C, U1.29 (PB10)
unnamed: SJ1.2, U1.37 (PC6)
unnamed: SJ3.2, U1.38 (PC7)
unnamed: SJ2.2, U1.39 (PC8)
unnamed: LED2.A, R5.2
unnamed: Q2.1 (G), U1.57 (PB5)
unnamed: Q3.1 (G), U1.58 (PB6)
unnamed: Q4.1 (G), U1.59 (PB7)
unnamed: Q5.1 (G), U1.33 (PB12)
unnamed: Q6.1 (G), U1.34 (PB13)
unnamed: Q7.1 (G), U1.35 (PB14)
unnamed: Q8.1 (G), U1.36 (PB15)
unnamed: R20.2, U1.28 (PB2)
unnamed: Q2.3 (D), R13.2, X3.5
unnamed: Q3.3 (D), R14.2, X3.9
unnamed: Q4.3 (D), R15.2, X3.6
unnamed: Q5.3 (D), R16.2, X3.2
unnamed: Q6.3 (D), R17.2, X3.4
unnamed: Q7.3 (D), R18.2, X3.3
unnamed: Q8.3 (D), R19.2, X3.1
NRST: C4.1, JP1.4, R2.1, U1.7 (NRST)
SWCLK: JP1.5, U1.49 (PA14)
SWDIO: JP1.6, U1.46 (PA13)
USB_DM: U1.44 (PA11), X2.2
USB_DP: U1.45 (PA12), X2.3
VCC: C1.1, C2.1, IC1.3 (IN), JP1.1, R13.1, R14.1, R15.1, R16.1, R17.1, R18.1, R19.1, X2.1, X3.7
VDD: BOOT0.3, C3.1, C5.1, C6.1, C9.1, C10.1, C11.1, C12.1, C13.1, C14.1, C15.1, C16.1, IC1.2 (OUT), IC1.TAB (OUT1), JP1.3, PA9BOOT.3, R2.2, R4.1, R5.1, SJ1.3, SJ2.3, SJ3.3, U1.1 (VBAT), U1.13 (VDDA), U1.19 (VDD_4), U1.32 (VDD_1), U1.48 (VDD_2), U1.64 (VDD_3)

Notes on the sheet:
1.0.0
HID2AMI Full: an awesome HID to Quadrature machine
PA2-> L "Deluxe Board" PA2-> H "Basic Board"
BOOT1

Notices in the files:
README.md:
LICENSE TERMS:
[License: CC BY-NC-SA 4.0](https://creativecommons.org/licenses/by-nc-sa/4.0/)
of HID2AMI are open source, released under the Creative Commons CC BY-NC license.
ShareAlike | If you remix, transform, or build upon the material, you must distribute your contributions under the same license as the original.
Board/HID2AMI.Deluxe.Rev2.0.0.brd:
HID2AMI 2.0.0 ©2021  EmberHeavyIndustries
